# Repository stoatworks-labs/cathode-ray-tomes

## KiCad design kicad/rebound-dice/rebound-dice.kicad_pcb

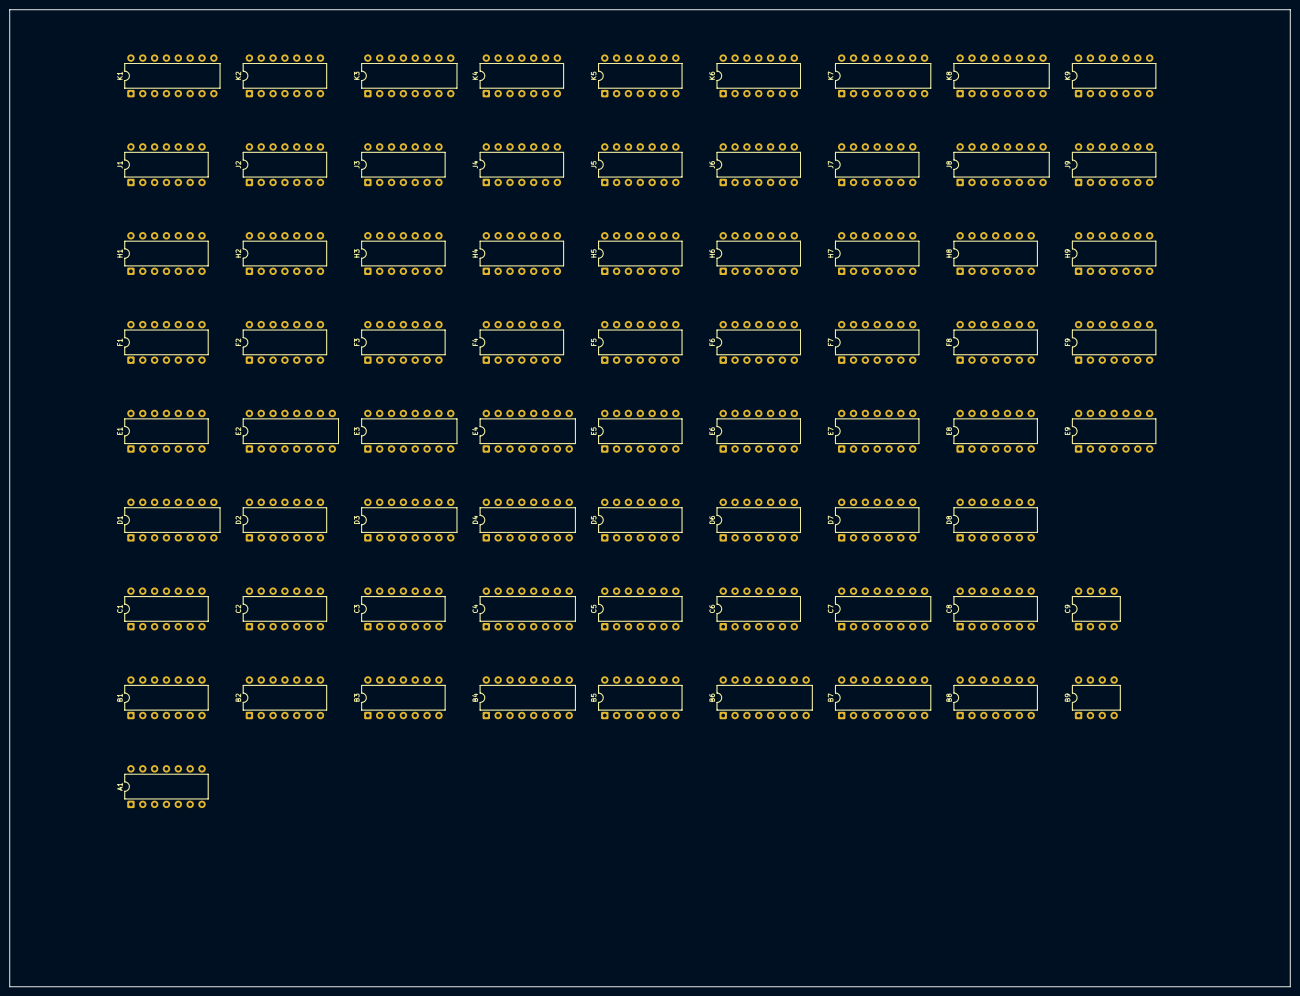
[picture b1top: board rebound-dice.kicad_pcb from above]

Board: 2 copper layers, 274.6 x 209.5 mm, 72 parts (0 on the bottom side), 226 nets, no tracks yet.

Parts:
A1: 7400; DIP-14_W7.62mm
B1: 7400; DIP-14_W7.62mm
B2: 7474; DIP-14_W7.62mm
B3: 74107; DIP-14_W7.62mm
B4, B7: 9316; DIP-16_W7.62mm
B5: 7404; DIP-14_W7.62mm
B6: 9322; DIP-16_W7.62mm
B8: 7410; DIP-14_W7.62mm
B9: 555; DIP-8_W7.62mm
C1: 7493; DIP-14_W7.62mm
C2: 7450; DIP-14_W7.62mm
C3: 7410; DIP-14_W7.62mm
C4, C7: 9316; DIP-16_W7.62mm
C5: 7486; DIP-14_W7.62mm
C6: 7474; DIP-14_W7.62mm
C8: 7402; DIP-14_W7.62mm
C9: 555; DIP-8_W7.62mm
D1: 9602; DIP-16_W7.62mm
D2: 7402; DIP-14_W7.62mm
D3, D4: 9316; DIP-16_W7.62mm
D5, D7: 7400; DIP-14_W7.62mm
D6, D8: 7474; DIP-14_W7.62mm
E1: 7400; DIP-14_W7.62mm
E2: 7483; DIP-16_W7.62mm
E3: 9316; DIP-16_W7.62mm
E4: 74193; DIP-16_W7.62mm
E5: 7408; DIP-14_W7.62mm
E6: 7402; DIP-14_W7.62mm
E7, E8: 7474; DIP-14_W7.62mm
E9: 7404; DIP-14_W7.62mm
F1: 7474; DIP-14_W7.62mm
F2, F7: 7408; DIP-14_W7.62mm
F3: 74107; DIP-14_W7.62mm
F4: 7420; DIP-14_W7.62mm
F5: 7493; DIP-14_W7.62mm
F6, F8: 7410; DIP-14_W7.62mm
F9: 7404; DIP-14_W7.62mm
H1: 7400; DIP-14_W7.62mm
H2, H7: 7410; DIP-14_W7.62mm
H3, H5: 7493; DIP-14_W7.62mm
H4, H9: 74107; DIP-14_W7.62mm
H6: 7427; DIP-14_W7.62mm
H8: 7430; DIP-14_W7.62mm
J1, J2, J4: 7474; DIP-14_W7.62mm
J3: 7493; DIP-14_W7.62mm
J5: 7486; DIP-14_W7.62mm
J6: 7400; DIP-14_W7.62mm
J7: 7410; DIP-14_W7.62mm
J8: 74153; DIP-16_W7.62mm
J9: 7490; DIP-14_W7.62mm
K1: 9602; DIP-16_W7.62mm
K2: 7493; DIP-14_W7.62mm
K3: 9316; DIP-16_W7.62mm
K4: 7400; DIP-14_W7.62mm
K5: 7474; DIP-14_W7.62mm
K6: 7402; DIP-14_W7.62mm
K7: 7448; DIP-16_W7.62mm
K8: 74153; DIP-16_W7.62mm
K9: 7490; DIP-14_W7.62mm

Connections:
+5V: A1.14, B1.14, B2.14, B3.14, B4.16, B5.14, B6.16, B7.16, B8.14, B9.8, C1.5, C3.14, C4.16, C5.14, C6.14, C7.16, C8.14, C9.8, D2.14, D3.16, D4.16, D5.14, D6.14, D7.14, D8.14, E1.14, E2.5, E3.16, E4.16, E5.14, E6.14, E7.14, E8.14, E9.14, F1.14, F2.14, F3.14, F4.14, F5.5, F6.14, F7.14, F8.14, F9.14, H1.14, H2.14, H3.5, H4.14, H5.5, H6.14, H7.14, H8.14, H9.14, J1.14, J2.14, J3.5, J4.14, J5.14, J6.14, J7.14, J8.16, J9.5, K2.5, K3.16, K4.14, K5.14, K6.14, K7.16, K8.16, K9.5
A1-1: A1.1, C2.6
A1-4: A1.4, C8.1, E7.13
A1-5: A1.5, E9.12
A1-6: A1.6, E7.3
A1-13: A1.13, C2.8
ATTRACT: D7.1, D8.3, D8.11, E7.2, E8.5
ATTRACT_n: A1.2, A1.12, D7.10, D7.12, E8.6, F2.10, F7.4, F7.10
B1-8: B1.8, E5.2
B1-11: B1.11, K6.8
B2-5: B2.5, C2.9
B2-6: B2.6, C2.5
B2-8: B2.8, B8.13
B2-10: B2.10, B5.11, K4.6
B3-3: B3.3, J2.2, J5.2
B4-9: B4.9, B5.8
B4-15: B4.15, B5.9, E4.4
B5-1: B5.1, B6.9
B5-2: B5.2, D5.2, E5.10
B5-4: B5.4, F7.1, K4.12
B5-5: B5.5, C5.8, D5.9
B5-6: B5.6, D5.13
B6-2: B6.2, C7.11
B6-3: B6.3, B7.11
B6-4: B6.4, C5.4, C6.2
B6-5: B6.5, C7.12
B6-6: B6.6, B7.12
B6-7: B6.7, D6.12
B6-12: B6.12, C6.12
B6-13: B6.13, B7.13
B6-14: B6.14, C7.13
B7-7: B7.7, B8.10, D7.8
B7-9: B7.9, B8.9, C8.10
B7-15: B7.15, D7.9
B8-4: B8.4, C7.7, D7.11
B8-5: B8.5, C7.9, C8.4
B9-3: B9.3, C8.9
BACKWARDS_n: D6.5, F1.1
BALL: B3.12, D5.1, E6.2, E6.3, E6.4
BALL_RETURN: C1.2, C1.3, E5.1, J5.3, K1.12
BALL_n: D2.5, E6.1
BP_n: C6.8, F2.1
C1-1: C1.1, C1.12
C1-8: C1.8, D2.8
C1-14: C1.14, D1.9
C2-1: C2.1, C2.2, D2.3, D2.4
C2-4: C2.4, C2.10, D2.2, D2.13
C3-1: C3.1, D4.12
C3-2: C3.2, D4.11
C3-3: C3.3, D3.15, F3.12, F4.10
C3-4: C3.4, F3.3, F4.9
C3-5: C3.5, D3.7, E3.15
C3-6: C3.6, D3.9, E3.9
C3-8: C3.8, H6.11
C3-12: C3.12, E6.6
C3-13: C3.13, C4.15, D5.4, F1.11
C4-7: C4.7, D4.15, D5.5
C4-9: C4.9, D4.9, D5.6
C4-14: C4.14, E1.1
C5-1: C5.1, D6.9
C5-3: C5.3, E5.4
C5-6: C5.6, D6.2
C5-11: C5.11, E4.15
C5-13: C5.13, C6.9
C6-1: C6.1, C6.13, D5.11, D6.10
C6-4: C6.4, C6.10, D5.8, D6.13
C7-15: C7.15, D7.13
C8-2: C8.2, E9.10
C8-3: C8.3, D7.2, D8.9
C8-5: C8.5, C9.3
CLK: D3.2, E3.2, H5.14, J4.5
CLK_n: J4.2, J4.6, J4.11
CP_n: D6.8, F2.13
D1-6: D1.6, E1.9
D1-7: D1.7, K1.5
D1-12: D1.12, E1.2, F1.8
D2-9: D2.9, E5.3
D2-10: D2.10, D2.11
D4-3: D4.3, E4.3
D4-4: D4.4, E4.2
D4-5: D4.5, E4.6
D4-6: D4.6, E4.7
D7-4: D7.4, D8.8
D7-6: D7.6, E8.1
D8-1: D8.1, D8.13, E9.11
D8-5: D8.5, D8.12
D8-10: D8.10, E8.4, E9.4
DISP_PAD1_n: B6.11, B8.6
DISP_PAD2_n: B6.10, B8.8
DP: C5.2, C5.12, C6.5, H1.9
E1-3: E1.3, E1.4
E1-5: E1.5, F2.8
E1-8: E1.8, F2.9
E1-11: E1.11, E2.11
E1-12: E1.12, E1.13, E2.3, H1.8
E2-2: E2.2, E3.5
E2-6: E2.6, E3.4
E2-8: E2.8, F2.11
E2-9: E2.9, E3.3
E2-10: E2.10, F2.3
E2-15: E2.15, E3.6
E3-11: E3.11, F4.12
E3-12: E3.12, F4.13
E4-1: E4.1, E5.6
E4-11: E4.11, E5.11
E5-13: E5.13, E6.13
E6-5: E6.5, F4.8
E7-5: E7.5, E7.12
F1-2: F1.2, F1.6, F2.5
F2-2: F2.2, F2.6, F2.12, H1.10
F4-6: F4.6, J4.12
F6-6: F6.6, F7.5
F6-8: F6.8, F7.9
F6-12: F6.12, F9.9
F7-3: F7.3, K5.13
F7-11: F7.11, J6.1
F7-13: F7.13, F9.6
F8-2: F8.2, H9.3
F8-4: F8.4, H9.5
F8-6: F8.6, J6.10
F8-8: F8.8, H8.12
F8-9: F8.9, K7.13
F8-10: F8.10, F9.4, H7.1, H7.3, J7.1
F8-11: F8.11, H6.12
F8-12: F8.12, J6.9
F9-8: F9.8, H7.11, H7.13
GND: A1.7, B1.7, B2.7, B3.7, B4.5, B4.6, B4.8, B5.7, B6.8, B6.15, B7.3, B7.4, B7.5, B7.6, B7.8, B8.7, B9.1, C1.10, C3.7, C4.3, C4.4, C4.5, C4.6, C4.8, C5.7, C6.7, C7.3, C7.4, C7.5, C7.6, C7.8, C8.7, C9.1, D1.4, D2.7, D3.5, D3.6, D3.8, D4.8, D5.7, D6.7, D7.7, D8.7, E1.7, E2.1, E2.12, E2.13, E2.16, E3.8, E4.8, E4.14, E5.7, E6.7, E6.12, E7.7, E8.7, E9.7, F1.7, F2.7, F3.7, F4.7, F5.10, F6.7, F7.7, F8.7, F9.7, H1.7, H2.7, H3.10, H4.7, H5.10, H6.7, H7.7, H8.7, H9.7, J1.7, J2.7, J3.10, J4.7, J5.7, J6.7, J7.7, J8.1, J8.8, J8.15, J9.6, J9.7, J9.10, K2.10, K3.8, K4.7, K5.2, K5.3, K5.7, K6.3, K6.7, K7.8, K8.1, K8.8, K8.15, K9.6, K9.7, K9.10
H1: B7.2, C7.2, E6.9, H5.1, H5.12
H1-3: H1.3, H1.12
H1-4: H1.4, K2.9, K3.4
H1-5: H1.5, K2.11, K3.6
H1-6: H1.6, J1.1
H1-13: H1.13, H2.6
H2: B2.11, H5.9, J2.3
H2-8: H2.8, K4.4, K6.9
H2-12: H2.12, J2.12
H4: F4.4, H5.8, H6.4, J6.13
H6-2: H6.2, H6.3, K6.1, K6.12
H6-6: H6.6, J7.10, J7.13
H6-8: H6.8, J1.11
H7-2: H7.2, K7.14
H7-4: H7.4, J7.4, K6.13
H7-5: H7.5, K7.12
H7-6: H7.6, H8.3
H7-8: H7.8, H8.2
H7-9: H7.9, K7.10
H7-12: H7.12, H8.11
H8: F5.14, H5.11, H6.5, J6.12
H8-4: H8.4, J7.12
H8-5: H8.5, J7.6
H8-6: H8.6, J7.8
H9-2: H9.2, J8.4, J8.12, K8.12
H9-6: H9.6, J8.6, J8.10, K8.10
H9-9: H9.9, J8.11, K9.11
H9-12: H9.12, J8.13, J9.11
H16: F5.1, F5.12, F6.4, F6.13, K4.2, K5.11, K6.2
H32: F5.9, F6.10, J8.14, K4.13, K8.14
H64: B5.3, C3.11, F4.1, F5.8, F6.11, J5.10, J8.2, K4.1, K8.2
H128: C3.10, F4.2, F5.11, F6.5, F6.9, H4.12, J5.12
H256: B2.12, B3.1, B6.1, B8.1, C2.3, F4.5, F6.3, H4.3, J5.13
H256_n: B2.2, B3.4, C2.13, C3.9, C5.5, C8.8, H4.2, J5.9
HBLANK: C8.6, F7.2, K5.5
HBLANK_n: B1.9, K5.6
HIT: B2.3, C6.3, C6.11, D6.3, D6.11, E6.10, E6.11
HIT_n: B4.1, D5.3, E6.8, F1.12, F1.13
HRESET: F5.2, F5.3, H5.2, H5.3, J2.11, J3.14, J4.8
HRESET_n: B9.2, C9.2, H4.13, J4.9, K5.4
HSYNC_n: C4.2, D4.2, K5.8
J1-2: J1.2, J1.6
J1-3: J1.3, K1.9
J1-5: J1.5, K2.14
J2-5: J2.5, J5.1
J5-8: J5.8, J6.5
J5-11: J5.11, J6.4
J6-3: J6.3, K6.5
J6-6: J6.6, K6.6
J6-11: J6.11, K6.11
J7-2: J7.2, K7.15
J7-5: J7.5, K7.11
J7-9: J7.9, K7.9
J8-3: J8.3, J9.8
J8-5: J8.5, K9.8
J8-7: J8.7, K7.2
J8-9: J8.9, K7.6
J9-9: J9.9, K8.13
K2-1: K2.1, K2.12
K2-8: K2.8, K3.5
K3-7: K3.7, K4.5, K4.8
K3-15: K3.15, K4.9
K4-3: K4.3, K5.1
K4-11: K4.11, K5.12
K6-4: K6.4, K7.4
K7-1: K7.1, K8.9
K7-7: K7.7, K8.7
K8-11: K8.11, K9.9
LEFT_SCORE: A1.3, K9.14
LSB1: C5.9, F8.5, K8.5, K9.1, K9.12
LSB2: C5.10, F8.1, J9.1, J9.12, K8.3
MISS_n: D1.5, D2.1
NET_HEIGHT_n: B1.10, B5.10
NET_n: B8.12, H8.1
PADDLE_12: B8.3, B8.11, K6.10
RIGHT_SCORE: A1.11, J9.14
SERVE: D2.12, D5.10, D5.12, J1.8, K2.2, K2.3
SERVE_TIME_n: D6.1, E5.12, J1.12, J1.13, K1.7
SERVE_n: B3.13, C4.1, D3.1, D4.1, E3.1, E4.10, E5.5, F1.10, F3.13, J1.9, J2.4, K1.11
START: D7.5, E7.9, J9.2, J9.3, K1.4, K9.2, K9.3
START_n: E7.1, E7.8, H9.10, H9.13
STOP: E8.3, J6.8
STOP1_n: C9.4, F7.8
STOP2_n: B9.4, F7.6
V1: H2.13, J3.1, J3.12
V2: H2.5, J3.9
V4: B8.2, E5.9, F6.2, H2.2, H2.4, H6.13, J3.8, K3.2
V8: B1.13, F6.1, H2.3, H3.14, H6.1, J3.11
V16: B1.12, F9.3, H3.1, H3.12, H7.10, J7.3, J7.11
V32: E1.10, F7.12, H2.10, H3.9
V64: B4.2, C8.11, C8.12, H2.11, H3.8
V64_n: C8.13, H6.10, J6.2
V128: F9.5, H2.9, H3.11, H4.9, H6.9, K3.9, K4.10
V256: E7.11, H2.1, H4.5
V256_n: D2.6, H4.6
VCC: B2.1, B2.4, B2.13, B4.3, B4.4, B4.7, B4.10, B7.1, B7.10, C4.10, C7.1, C7.10, D1.3, D1.11, D1.13, D3.3, D3.4, D3.10, D4.7, D6.4, D8.2, E2.4, E2.7, E3.7, E3.10, E4.5, E4.9, E7.4, E7.10, E8.2, F1.4, F3.1, F3.4, H4.1, H4.4, H4.8, H4.11, H9.1, H9.4, H9.8, H9.11, J1.4, J1.10, J2.1, J2.10, J2.13, J4.1, J4.4, J4.10, J4.13, K1.3, K1.13, K3.1, K3.3, K3.10, K5.10, K7.3, K7.5, K8.4, K8.6
VRESET: F1.3, F2.4, H3.2, H3.3, J2.8, J3.2, J3.3
VRESET_n: H1.1, H4.10, J2.9
VSYNC_n: D4.10, H1.2, H1.11
